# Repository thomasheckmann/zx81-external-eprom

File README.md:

# ZX81 external eprom
The primary aim of this project is to enable the use of an upgraded version of the ZX81 ROM without requiring the ZX81 to be opened up for ROM replacement. I decided upon the W27C512 EEPROM, allowing storage of 8 x 8kb ROMs, each selectable via dip switches.

# the prototype
It all started with a breadboard and a lot of wires! It is chaos, yes, but it turned out to work as intended. With this PoC it is possible to run a ZX81 with a custom ROM externally, without the need to open and replace the original ROM chip. It does however stil needs the original ROM inside the ZX81, but mainly because of the way the display system works on the ZX81 - it's clever, but at the same time a main challenge these days.

# version 1.0
Basic version, requires the original ROM in the ZX81 - because of the way the display system works.
KiCad 8 files available as well as Gerber files for PCB production.

BOM for v1.0:
- [ ] WINBOND W27C512 EEPROM
- [ ] 74LS138
- [ ] 3 x 10K Resistors
- [ ] BC549 Transistor
- [ ] 2 x 100nF ceramic capacitor, 2,5mm
- [ ] DIP Switch 3 x ON-OFF
- [ ] Sockets for IC, Edge Connector (RM 2,54)

The PCB can be fitted with a standard Edge Connector for ZX81, or it can be used as a plug-in card in the [Bus Extender](https://github.com/thomasheckmann/zx81-bus-extender)

## Planned changes / improvement for v1.1
- The silkscreen says 4K7 for the resistors, but with the WINBOND they can all be changed to 10K (as in this picture).
- The DIP switches from left to right are, A13, A14, A15 - but should really be the other way around, to match the binary pattern and bank number in EEPROM.
- Support for 16kb ROM, needed to run SPonZY (ZX Spectrum ROM modified to run on ZX81 Hardware).
- Rotate the ICs 180 degree, just to make the text in the right direction (I know - it's not important, but...)

# version 1.1
A version with the changes mentioned above was produced, it worked out OK - but as I already had a few other changes in mind, it was never released as such. But for the curious minds, here are some pictures of how it looked like - and as can be seen, it runs the SPonZY ROM quite well :-)

| <!---> | <!---> |
| ------ | ------ |
|||
|||

# version 1.2
Getting close to the final version of external ROM switcher for support for 8KiB or 16KiB banks. Changes from 1.1 to the board:
- Making PADS 2mm longer, to prevent potential issues with some connectors (when used in the Expander board)
- Changed from pull-ups to pull-downs, to match actual behaviour of DIP-SWITCH (up = 1/ON/HIGH, down = 0/OFF/LOW)

| SCHEMA | PCB |
| ------ | --- |
|||

BOM change:
- [ ] DIP Switch 4 x ON-OFF

## Instructions on how to use

- DIP-4 (right) - sets the mode of operation, DOWN = use 8KiB banks, UP = use 16KiB banks
- DIP-1 to 3, selects which banks is used as ROM - in case of 16KiB banking, DIP-3 (A13) is ignored.

## How to create image for EEPROM
The W27C512 EEPROM can contain 8x 8KiB or 4 x 16KiB images - selectable with the switch, forming the binary number 0-3 or 0-7 for the active bank.

For Windows
```
COPY /B ROM_0+ROM_1+ROM_2+ROM_3 IMAGE.BIN
```

For Unix/Mac
```
cat ROM_0 ROM_1 ROM_2 ROM_3 >IMAGE.BIN
```

Use your favorite (E)EPROM programmer to transfer the IMAGE.BIN to the EEPROM

8K roms - DIP4: OFF/DOWN
A15|A14|A13|ROM
---|---|---|---
OFF | OFF | OFF | 0: ROM_0
OFF | OFF | ON  | 1: ROM_1
OFF | ON  | OFF | 2: ROM_2
OFF | ON  | ON  | 3: ROM_3
ON  | OFF | OFF | 4: ROM_4
ON  | OFF | ON  | 5: ROM_5
ON  | ON  | OFF | 6: ROM_6
ON  | ON  | ON  | 7: ROM_7

16K roms - DIP4: ON/UP
A15|A14|A13|ROM
---|---|---|---
OFF | OFF | - | 0: ROM_0
OFF | ON  | - | 1: ROM_1
ON  | OFF | - | 2: ROM_2
ON  | ON  | - | 3: ROM_3

# 16K ROM - what? why?
Only one known 16K rom exists, it's the SPonZY [SPeccy ON Zeddy](https://www.sinclairzxworld.com/viewtopic.php?t=465) ROM which turns your ZX81 into a ZX Spectrum (without color and sound of course). Just put the ROM file on the EPROM, set DIP 4 to ON/UP and power up your ZX81.

## SPECIAL ROMs
A few ROMs from different interfaces does not sit in the 0-8K memory space, using the 16K configuration of this interface - it is possible to get them running on your ZX81. The following sections provides instruction on how to run the ones I know of.

## Timex Store Demonstrator ROM
To run the [ROM](http://zx81.ordi5.free.fr/CartesZx81/Timex/StoreDemonstrator/) from the Timex Store Demonstrator Board, the setup needs to be like this:
- 0-8K, 8K ROM - ZX81 rom, use v2 - 649 (MD5: db398d4e4e93a6d4dee3bfe146918219)
- 8-16K, 8K DemoStore ROM

Modify ZX81 rom - Change byte offset 0x09DB from 0x40 to 0x20 (ZX81v2_mod.rom)

Unix/MacOS
````
cat ZX81v2_mod.rom StoreDemo.rom >SD.rom
cat SD.rom SD.rom SD.rom SD.rom > SDx4.rom
````
Resulting SD.rom shoulb be a 16K rom image and SDx4.rom should be 64K (contains SD.rom in all 4 banks), ready to be programmed in W27C512.
To start the demo program, run type RUN

## Memotech MemoCalc
This is a 4K rom that resides in the upper 4K of the mirror area. Layout of a 16K rom containing this, should be:
- 0-8K, 8K ROM - ZX81 rom, use v2 - 649 (MD5: db398d4e4e93a6d4dee3bfe146918219)
- 8-12K, copy of first 4K of the ZX81 ROM
- 12-16, the [MemoCalc Rom](https://www.zx81stuff.org.uk/zx81/hardware/Memocalc)

Unix/MacOS
````
split -b 4k ZX81v2.rom ZX81
cat ZX81v2.rom ZX81aa Memocalc.rom >MC.rom
cat MC.rom MC.rom MC.rom MC.rom > MCx4.rom
````
Resulting MC.rom is the 16K image and MCx4.rom should be 64K (contains MC.rom in all 4 banks).

MemoCalc is started with RAND USR 13824

## TS 1510 Command Cartridge Player
A ROM Catridge interface for the TS1000/1500 - only 4 cartidges was produced, 3 8K and 1 16K

To use the 8K Catridge - the layout of the 16K rom should be:
- 0-8K, 8K ROM - ZX81, use v2 - 649 (MD5: db398d4e4e93a6d4dee3bfe146918219) (or the TS1500 rom, not tested yet)
- 8-16K, the Catridge ROM

Unix/MacOS
````
cat ZX81v2.rom chess.rom > TS1510_CHESS.rom
cat TS1510_CHESS.rom TS1510_CHESS.rom TS1510_CHESS.rom TS1510_CHESS.rom > TS1510_CHESSx4.rom
````
When ZX81 has booted up, start the game with RAND USR 8192. If using the TS1500 ROM - the cartridge will autostart, as the TS1500 ROM has been changed a bit to handle this.

## ASDIS
[ASDIS](https://www.zx81.de/soft/asdis_bs.htm) - Assembler/Disassembler - 8K ROM [ASDIS.C](https://www.zx81.de/soft/swd_asdi.htm)

Layout:
- 0-8K, 8K ROM - ZX81 rom, use v2 - 649 (MD5: db398d4e4e93a6d4dee3bfe146918219)
- 8-16K, ASDIS.C Rom image

Unix/MacOS
````
cat ZX81v2.rom ASDIS.C > ASDIS.rom
cat ASDIS.rom ASDIS.rom ASDIS.rom ASDIS.rom >  ASDISx4.rom
````
When ZX81 has booted up, start the assembler/disassembler with RAND USR 8192

## AUTO RUN a (P)tape file
Yes, it's possible to make a setup which makes the ZX81 able to boot and auto run a tape file. Concept based on work by Wilf Rigter - look in the 'autorun' folder for more details.

OR you can checkout this awesome tool [ZX81 External EPROM Builder](https://github.com/general-ackbar/ZX81-external-eprom-builder), to create the required ROM file to burn into EPROM. The tool supports multiple P files (as long as it fits in 8K) together with a MENU to select program.

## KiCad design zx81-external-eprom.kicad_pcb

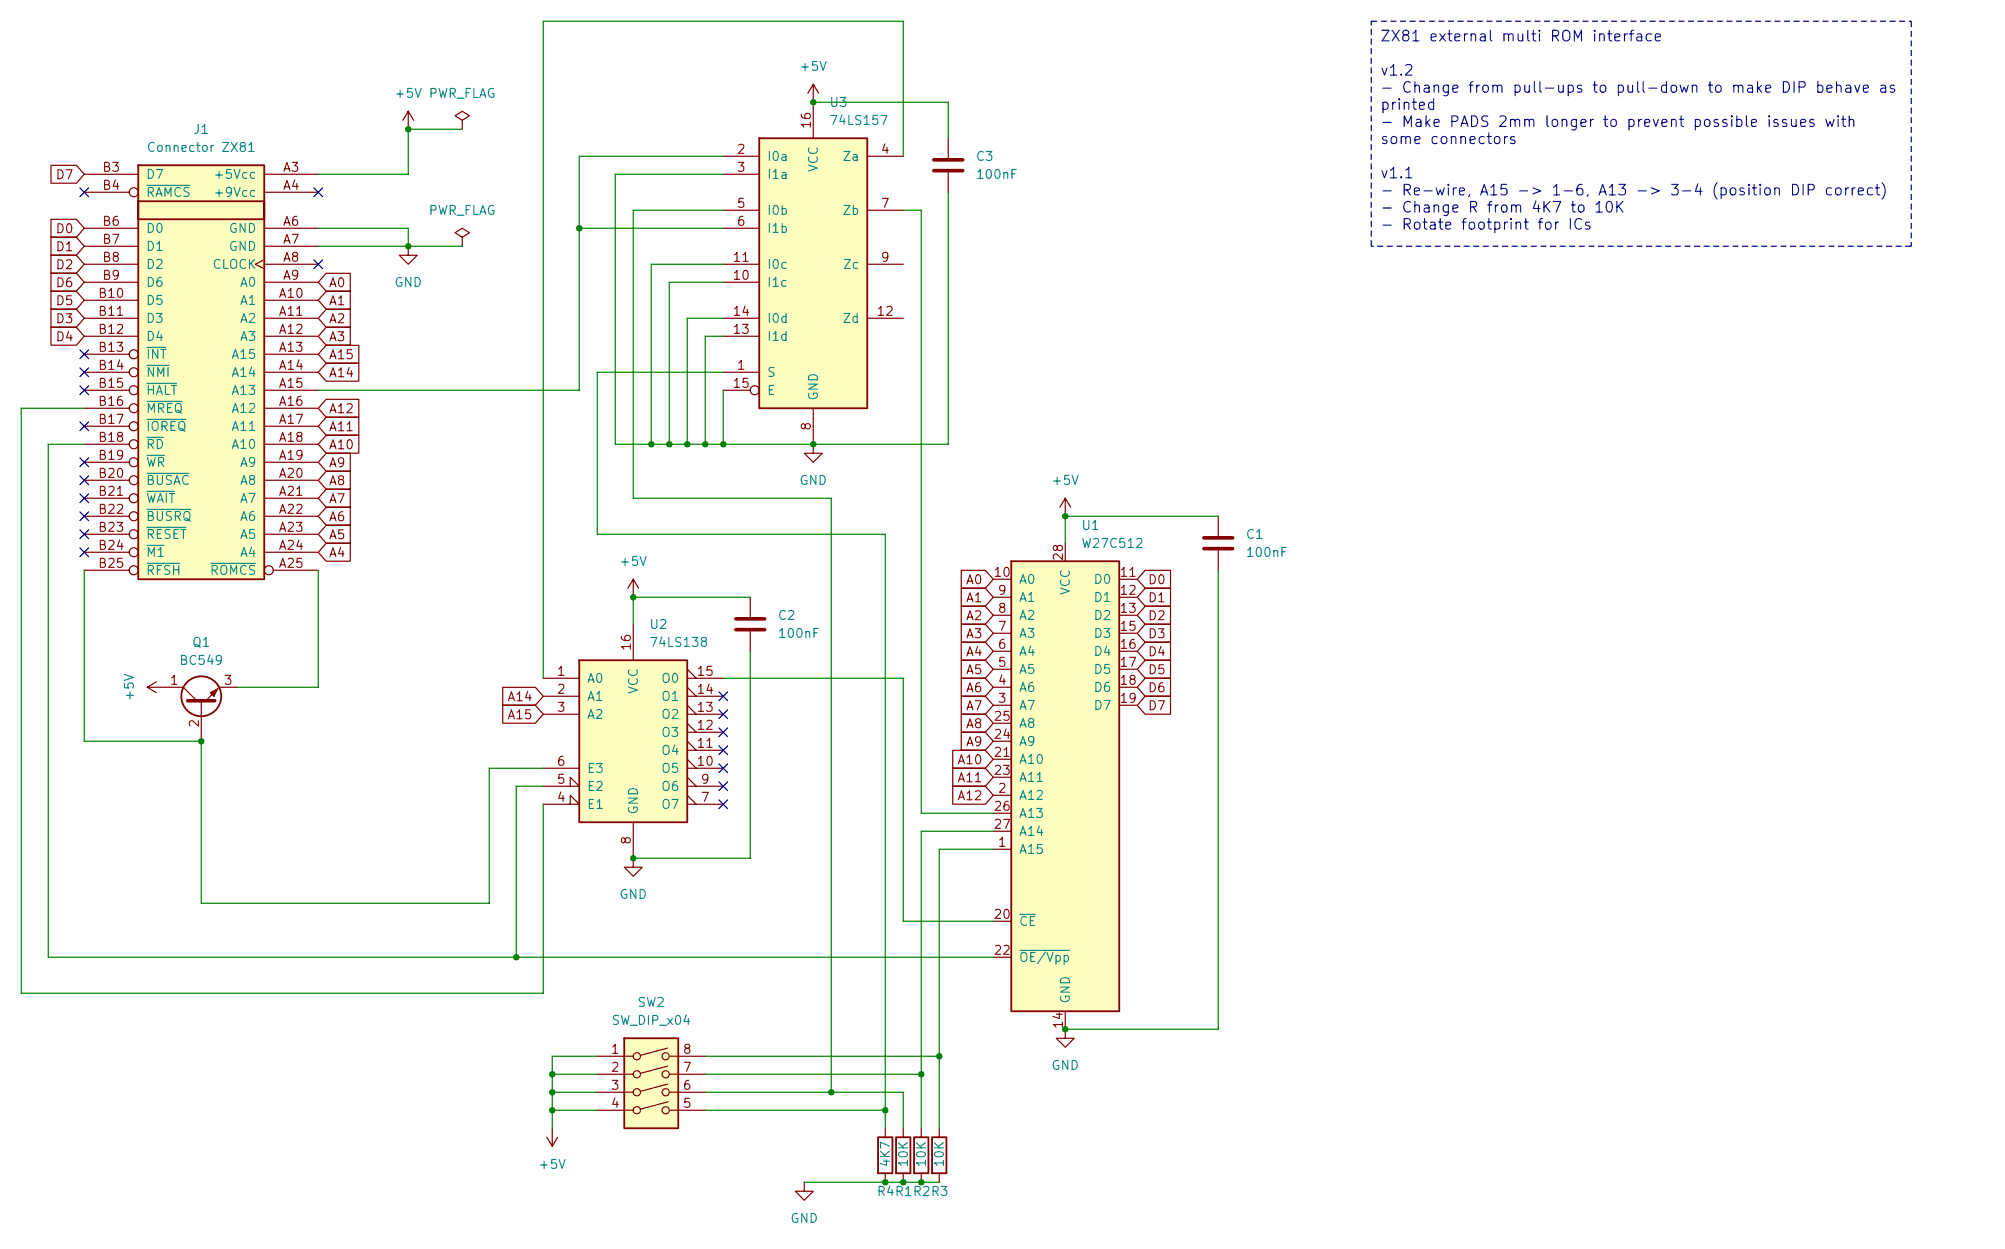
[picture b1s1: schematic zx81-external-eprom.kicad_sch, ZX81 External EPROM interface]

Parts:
C1, C2, C3: 100nF; C_Disc_D3.0mm_W1.6mm_P2.50mm
J1: Connector ZX81; EDGE ZX81 BOTTOM
Q1: BC549; TO-92_Inline
R1, R2, R3: 10K; R_Axial_DIN0207_L6.3mm_D2.5mm_P10.16mm_Horizontal
R4: 4K7; R_Axial_DIN0207_L6.3mm_D2.5mm_P10.16mm_Horizontal
SW2: SW_DIP_x04; SW_DIP_SPSTx04_Slide_6.7x11.72mm_W7.62mm_P2.54mm_LowProfile
U1: W27C512; DIP-28_W15.24mm
U2: 74LS138; DIP-16_W7.62mm
U3: 74LS157; DIP-16_W7.62mm

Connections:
+5V: C1.1, C2.1, C3.1, J1.A3 (+5Vcc), Q1.1 (C), SW2.1, SW2.2, SW2.3, SW2.4, U1.28 (VCC), U2.16 (VCC), U3.16 (VCC)
A0: J1.A9 (A0), U1.10 (A0)
A1: J1.A10 (A1), U1.9 (A1)
A2: J1.A11 (A2), U1.8 (A2)
A3: J1.A12 (A3), U1.7 (A3)
A4: J1.A24 (A4), U1.6 (A4)
A5: J1.A23 (A5), U1.5 (A5)
A6: J1.A22 (A6), U1.4 (A6)
A7: J1.A21 (A7), U1.3 (A7)
A8: J1.A20 (A8), U1.25 (A8)
A9: J1.A19 (A9), U1.24 (A9)
A10: J1.A18 (A10), U1.21 (A10)
A11: J1.A17 (A11), U1.23 (A11)
A12: J1.A16 (A12), U1.2 (A12)
A14: J1.A14, U2.2 (A1)
A15: J1.A13 (A15), U2.3 (A2)
D0: J1.B6 (D0), U1.11 (D0)
D1: J1.B7 (D1), U1.12 (D1)
D2: J1.B8 (D2), U1.13 (D2)
D3: J1.B11 (D3), U1.15 (D3)
D4: J1.B12 (D4), U1.16 (D4)
D5: J1.B10 (D5), U1.17 (D5)
D6: J1.B9 (D6), U1.18 (D6)
D7: J1.B3 (D7), U1.19 (D7)
GND: C1.2, C2.2, C3.2, J1.A6 (GND), J1.A7 (GND), R1.2, R2.2, R3.2, R4.2, U1.14 (GND), U2.8 (GND), U3.3 (I1a), U3.8 (GND), U3.10 (I1c), U3.11 (I0c), U3.13 (I1d), U3.14 (I0d), U3.15 (E)
unnamed: J1.A15 (A13), U3.2 (I0a), U3.6 (I1b)
unnamed: J1.B16 (~MREQ), U2.4 (E1)
unnamed: J1.B18 (~RD), U1.22 (~OE/Vpp), U2.5 (E2)
unnamed: J1.B25 (~RFSH), Q1.2 (B), U2.6 (E3)
unnamed: J1.A25 (~ROMCS), Q1.3 (E)
unnamed: U1.26 (A13), U3.7 (Zb)
unnamed: R2.1, SW2.7, U1.27 (A14)
unnamed: R3.1, SW2.8, U1.1 (A15)
unnamed: U1.20 (~CE), U2.15 (O0)
unnamed: U2.1 (A0), U3.4 (Za)
unnamed: R1.1, SW2.6, U3.5 (I0b)
unnamed: R4.1, SW2.5, U3.1 (S)

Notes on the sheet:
ZX81 external multi ROM interface v1.2 - Change from pull-ups to pull-down to make DIP behave as printed - Make PADS 2mm longer to prevent possible issues with some connectors v1.1 - Re-wire, A15 -> 1-6, A13 -> 3-4 (position DIP correct) - Change R from 4K7 to 10K - Rotate footprint for ICs

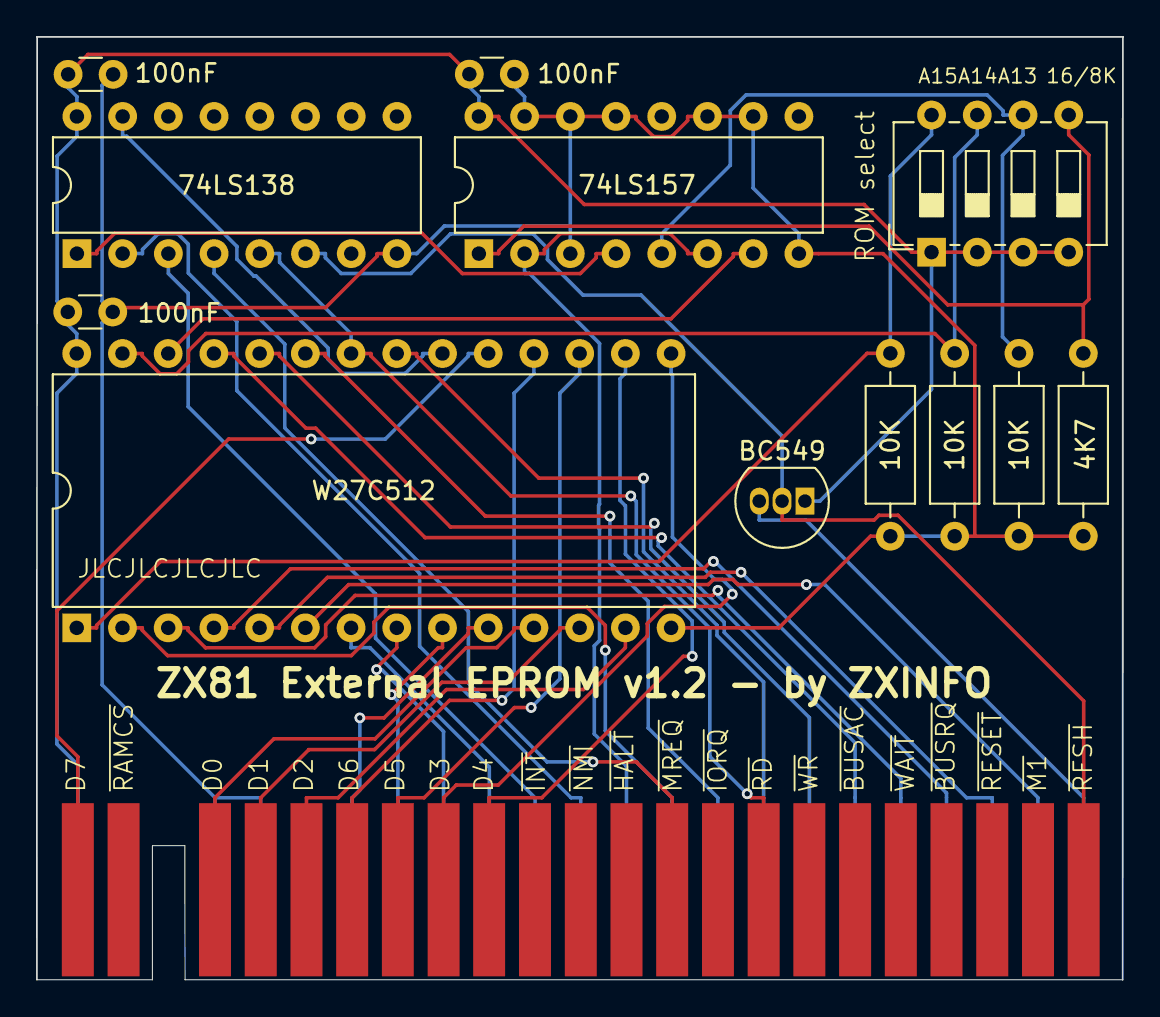
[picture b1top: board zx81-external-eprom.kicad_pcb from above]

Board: 2 copper layers, 60.3 x 52.4 mm, 13 parts (0 on the bottom side), 37 nets.

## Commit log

2024-04-14 Initial version v1
2024-04-14 small cosmetic changes
2024-04-14 cosmetic changes
2024-04-14 Local SYMBOL & FOOTPRINT
2024-04-15 small design fixes
2024-05-02 changed Resistor to 10K
2024-05-18 version 1.2
2024-05-21 Update README.md
    updated README
2025-08-09 First version for KiCad v9
2025-08-12 Autorun code
2025-08-12 clean up
2025-08-12 updated ignore
